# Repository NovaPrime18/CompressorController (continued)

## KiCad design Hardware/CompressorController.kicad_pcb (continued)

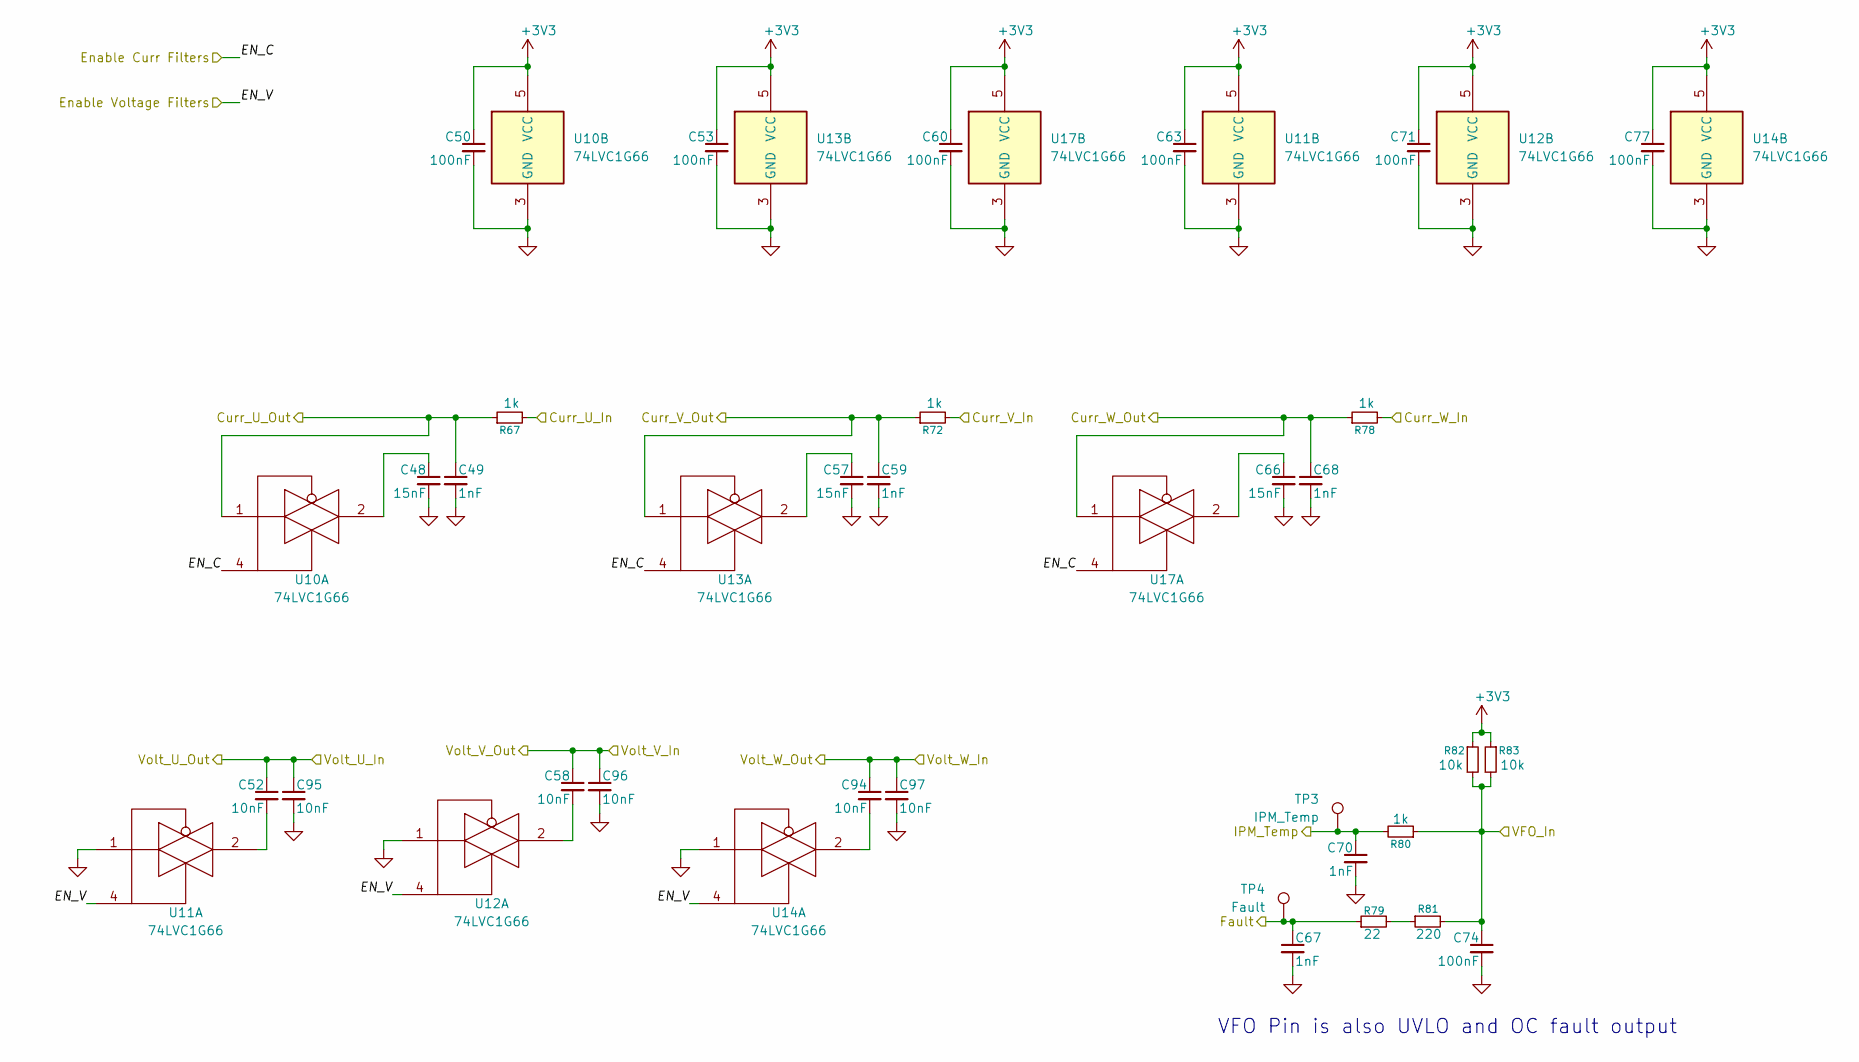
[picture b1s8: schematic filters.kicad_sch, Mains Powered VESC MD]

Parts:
C48, C57, C66: 15nF; C_0603_1608Metric; LCSC C1596
C49, C59, C67, C68, C70: 1nF; C_0603_1608Metric; LCSC C1588
C50, C53, C60, C63, C71, C74, C77: 100nF; C_0603_1608Metric; LCSC C14663
C52, C58, C94, C95, C96, C97: 10nF; C_0603_1608Metric; LCSC C1589
R67, R72, R78, R80: 1k; R_0603_1608Metric; LCSC C21190
R79: 22; R_0603_1608Metric; LCSC C23345
R81: 220; R_0603_1608Metric; LCSC C22962
R82, R83: 10k; R_0603_1608Metric; LCSC C25804
TP3: IPM_Temp; TestPoint_Pad_D1.5mm
TP4: Fault; TestPoint_Pad_D1.5mm
U10, U11, U12, U13, U14, U17: 74LVC1G66; SOT-353_SC-70-5; JLC C97489

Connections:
+3V3: C50.1, C53.1, C60.1, C63.1, C71.1, C77.1, R82.1, R83.1, U10.5 (VCC), U11.5 (VCC), U12.5 (VCC), U13.5 (VCC), U14.5 (VCC), U17.5 (VCC); also elsewhere on the board
/Filters/Curr_U_Out: C49.1, R67.1, U10.1; also elsewhere on the board
/Filters/Curr_V_Out: C59.1, R72.1, U13.1; also elsewhere on the board
/Filters/Curr_W_Out: C68.1, R78.1, U17.1; also elsewhere on the board
/Filters/EN_C: U10.4, U13.4, U17.4; also elsewhere on the board
/Filters/EN_V: U11.4, U12.4, U14.4; also elsewhere on the board
/Filters/Fault: C67.1, R79.1, TP4.1 (1_1); also elsewhere on the board
/Filters/IPM_Temp: C70.1, R80.2, TP3.1 (1_1); also elsewhere on the board
/Filters/VFO_In: C74.1, R80.1, R81.2, R82.2, R83.2; also elsewhere on the board
/Filters/Volt_U_In: C52.1, C95.1; also elsewhere on the board
/Filters/Volt_V_In: C58.1, C96.1; also elsewhere on the board
/Filters/Volt_W_In: C94.1, C97.1; also elsewhere on the board
/Phases/Curr_U: R67.2; also elsewhere on the board
/Phases/Curr_V: R72.2; also elsewhere on the board
/Phases/Curr_W: R78.2; also elsewhere on the board
GND: C48.2, C49.2, C50.2, C53.2, C57.2, C59.2, C60.2, C63.2, C66.2, C67.2, C68.2, C70.2, C71.2, C74.2, C77.2, C95.2, C96.2, C97.2, U10.3 (GND), U11.1, U11.3 (GND), U12.1, U12.3 (GND), U13.3 (GND), U14.1, U14.3 (GND), U17.3 (GND); also elsewhere on the board
unnamed: C48.1, U10.2
unnamed: C52.2, U11.2
unnamed: C57.1, U13.2
unnamed: C58.2, U12.2
unnamed: C66.1, U17.2
unnamed: C94.2, U14.2
unnamed: R79.2, R81.1

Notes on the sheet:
VFO Pin is also UVLO and OC fault output

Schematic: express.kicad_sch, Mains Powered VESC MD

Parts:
C31: 1uF; C_0603_1608Metric; LCSC C15849
C32, C33: 100nF; C_0603_1608Metric; LCSC C14663
C34: 10uF; C_0805_2012Metric; LCSC C440198
D4: BAV16W; D_SOD-123; JLC C459527
F2: 0.5A; R_0805_2012Metric; JLC C2833485
FB2: 600R@100MHz; L_0603_1608Metric; LCSC C1002
J7: Connector, USB-TYPE-C-16P; TYPE-C-SMD_HX-TYPE-C-16PIN; LCSC C2927039
R42, R43: 22; R_0603_1608Metric; LCSC C23345
R44, R45, R46, R47, R48, R49, R50: 10k; R_0603_1608Metric; LCSC C25804
SW1, SW2: KMR211NGLFS; SW_Push_1P1T_NO_CK_KMR2; JLC C221676
U8: ESP32-C3-WROOM-02; JLC C2934560

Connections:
+3V3: C32.1, C33.1, C34.1, R48.2, R49.2, R50.2, U8.1 (3V3); also elsewhere on the board
+5V: D4.1 (K); also elsewhere on the board
/CAN1/RX: U8.18 (IO0); also elsewhere on the board
/CAN1/TX: U8.17 (IO1); also elsewhere on the board
/WiFi & BT/EN: C31.2, R48.1, SW1.2, U8.2 (EN)
/WiFi & BT/USB_DN: R43.2, U8.13 (IO18)
/WiFi & BT/USB_DP: R42.2, U8.14 (IO19)
GND: C31.1, C32.2, C33.2, C34.2, J7.A12B1 (GND), J7.B12A1 (GND), J7.S1 (SHIELD), R44.2, R45.2, R46.2, R47.2, SW1.1, SW2.1, U8.9 (GND), U8.19 (GND); also elsewhere on the board
unnamed: D4.2 (A), FB2.1
unnamed: F2.1, FB2.2
unnamed: F2.2, J7.A9B4 (VBUS), J7.B9A4 (VBUS)
unnamed: J7.A5 (CC1), R46.1, R47.1
unnamed: J7.B5 (CC2), R44.1, R45.1
unnamed: J7.A6 (D+), J7.B6 (D+), R42.1
unnamed: J7.A7 (D-), J7.B7 (D-), R43.1
unnamed: R50.1, U8.16 (IO2)
unnamed: R49.1, U8.7 (IO8)
unnamed: SW2.2, U8.8 (IO9)

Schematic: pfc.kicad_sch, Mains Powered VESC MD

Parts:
C46, C55, C65: 10uF; C_0805_2012Metric; LCSC C440198
C51: 1.5uF; C_Rect_L24.0mm_W10.1mm_P22.50mm_MKT; partnm B32923C3155M; JLC C47279087
C54, C98: 2.7nF; C_0603_1608Metric; LCSC C1609
C56, C64: 100nF; C_0603_1608Metric; LCSC C14663
C61: 4.7uF; C_0603_1608Metric; LCSC C19666
C62: 390nF; C_0603_1608Metric; LCSC C376833
C69: 330pF; C_1808_4520Metric; not fitted
C72, C73, C75: 330uF; CP_Radial_D30.0mm_P10.00mm_SnapIn; LCSC C7211174
C76: 820pF; C_0603_1608Metric; LCSC C1632
D11: BAT54J; D_SOD-323F; LCSC C12744
D12: 1N5406; D_DO-201AD_P15.24mm_Horizontal; LCSC C38409
D13, D18, D19: MMSD914; D_SOD-123; LCSC C27975268
D14: BCA65S30D3; TO-247-2_Vertical; JLC C42401690
HS2: XSD683-022; HEATSINK-TH_L35.5-W11.0-XSD683-022; JLC C286231
L2: 330uH; IND-TH_L33.0-W15.6-P15.00-D1.5; LCSC C52766608
Q2: BC847C; Q_SOT-23; Part BC847C; LCSC C7420337; not fitted
Q3, Q4, Q5: IPL60R185C7; VSON-4_L8.1-W8.1-P2.00-BL; JLC C537028
R62, R63, R88, R89: 332k; R_1206_3216Metric; LCSC C49010117
R64, R90: 340k; R_1206_3216Metric; LCSC C2999478
R65, R76: 10k; R_0603_1608Metric; LCSC C25804
R66: 13.7k; R_0603_1608Metric; LCSC C22793; not fitted
R68: 220; R_0603_1608Metric; LCSC C22962
R69: 0.2; R_2512_6332Metric; LCSC C5375488
R70: 0.02; R_2512_6332Metric; LCSC C5375467
R71: 21.5k; R_0603_1608Metric; LCSC C22911
R73: 23.7k; R_0603_1608Metric; LCSC C22912
R74, R98, R101: 2; R_1206_3216Metric; LCSC C2907468
R75, R99, R102: 1; R_1206_3216Metric; LCSC C17928
R77: 43; R_2512_6332Metric; LCSC C2930460; not fitted
R84, R85, R86: 200k; R_1206_3216Metric; LCSC C17954
R87: 3.16k; R_0805_2012Metric; LCSC C52603
R91: 13k; R_0603_1608Metric; LCSC C22797
R92, R93, R94, R95: 221k; R_1206_3216Metric; LCSC C872617
TP5: HVDC-Sense; TestPoint_Pad_D1.5mm
TP6: ACSense; TestPoint_Pad_D1.5mm
U15: UCC28180D; SOIC-8_3.9x4.9mm_P1.27mm; JLC C88567
U16: UCC27517ADBV; SOT-23-5; JLC C2653784

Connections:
+15V: C55.1, C56.1, C64.1, C65.1, U15.7 (VCC), U16.1 (V_{DD}); also elsewhere on the board
/MCU/Bus Voltage: R86.2, R87.1; also elsewhere on the board
/PFC/AC Sense: C46.1, Q2.1 (B), R64.2, R65.1, TP6.1 (1_1)
/PFC/AC_sense: R62.1; also elsewhere on the board
/PFC/DC_Bus_In_+: C51.1, D12.2 (A), L2.1; also elsewhere on the board
/PFC/DC_Bus_In_-: C51.2, R68.1, R69.1, R70.1; also elsewhere on the board
/PFC/Vsense: C76.1, Q2.3 (C), R90.2, R91.1, TP5.1 (1_1), U15.6 (VSENSE)
/Phases/DC Bus +: C69.1, C72.1, C73.1, C75.1, D12.1 (K), D14.1 (K), R84.1, R88.1, R92.1, R94.1; also elsewhere on the board
GND: C46.2, C54.2, C55.2, C56.2, C61.2, C62.2, C64.2, C65.2, C72.2, C73.2, C75.2, C76.2, C98.2, D11.1 (K), Q3.2 (S), Q3.3 (S), Q3.4 (S), Q4.2 (S), Q4.3 (S), Q4.4 (S), Q5.2 (S), Q5.3 (S), Q5.4 (S), R66.2, R69.2, R70.2, R71.2, R76.2, R87.2, R91.2, R93.2, R95.2, U15.1 (GND), U16.2 (GND), U16.4 (IN-); also elsewhere on the board
unnamed: C61.1, R73.2
unnamed: C69.2, R77.2
unnamed: D11.2 (A), R65.2
unnamed: D13.2 (A), Q3.1 (G), R75.2
unnamed: D13.1 (K), R74.2, R75.1
unnamed: D14.2 (A), L2.2, Q3.5 (D), Q4.5 (D), Q5.5 (D), R77.1
unnamed: D18.2 (A), Q4.1 (G), R99.2
unnamed: D18.1 (K), R98.2, R99.1
unnamed: D19.2 (A), Q5.1 (G), R102.2
unnamed: D19.1 (K), R101.2, R102.1
unnamed: Q2.2 (E), R66.1
unnamed: R62.2, R63.1
unnamed: R63.2, R64.1
unnamed: R84.2, R85.1
unnamed: R85.2, R86.1
unnamed: R88.2, R89.1
unnamed: R89.2, R90.1
unnamed: R92.2, R93.1
unnamed: R94.2, R95.1
unnamed: R71.1, U15.4 (FREQ)
unnamed: U15.8 (GATE), U16.3 (IN+)
unnamed: C54.1, U15.2 (ICOMP)
unnamed: C98.1, R68.2, U15.3 (ISENSE)
unnamed: C62.1, R73.1, U15.5 (VCOMP)
unnamed: R74.1, R76.1, R98.1, R101.1, U16.5 (OUT)

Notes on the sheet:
Heatsink for D14
Following TIDA-00443
TI's Fet got quite hot (90C) So 3x parallel, and better FETs as well
IDk why, but TI ref design does this, trim?
Boost follower is actually quite a bit more efficient. But the software might not like the regulation loop.
Bleeder boys
TODO: REPLACE WITH SiC
Gate drive
PFC controller
Boost follower control and sensing

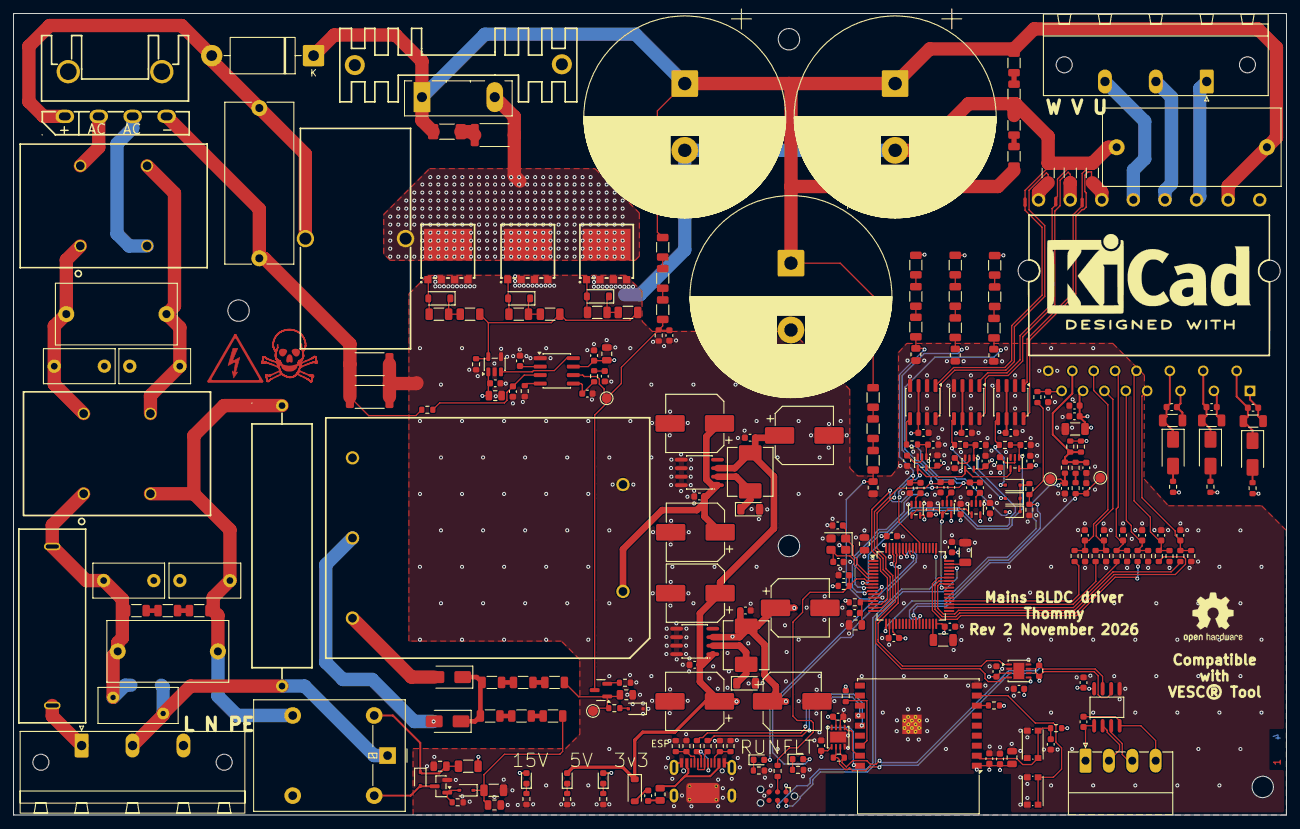
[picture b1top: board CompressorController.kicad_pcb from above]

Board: 4 copper layers, 190.6 x 120.0 mm, 279 parts (1 on the bottom side), 154 nets.

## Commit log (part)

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2026-04-03 test
2026-04-03 Added JLC part Nmrs, added a lot of footprints
2026-04-03 removed history
2026-04-03 cleanup
2026-04-03 final cleanup
2026-04-17 Added full PFC schematic
2026-04-17 Added the last components, and LCSC IDs.
2026-04-17 3v3 Buck, Heatsink for Bridge, 3x PFC FET
2026-04-18 Fixed ISENSE connection being high-side
2026-05-06 Placed components on board
2026-06-23 Routed the PCB
2026-06-23 Replace GNU GPL with CERN Open Hardware Licence
2026-06-23 Revise README for Mains Powered VESC Motor Driver
    Updated project name and expanded the overview section to provide detailed information about the VESC-compatible motor driver. Added key features, block diagram, schematic hierarchy, firmware details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
